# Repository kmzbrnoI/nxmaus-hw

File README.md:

# XNmaus

jednoduchý ovladač pro XpressNet

Důraz je kladen na nízkou výrobní cenu a dostupnost součástek.
Ovladač nemá display, adresa loko se mění jen vyjímečně.
Má jít o obdobu ovladače Fredi.

## Firmware

Program pro procesor je na adrese https://github.com/kmzbrnoI/nxmaus-fw

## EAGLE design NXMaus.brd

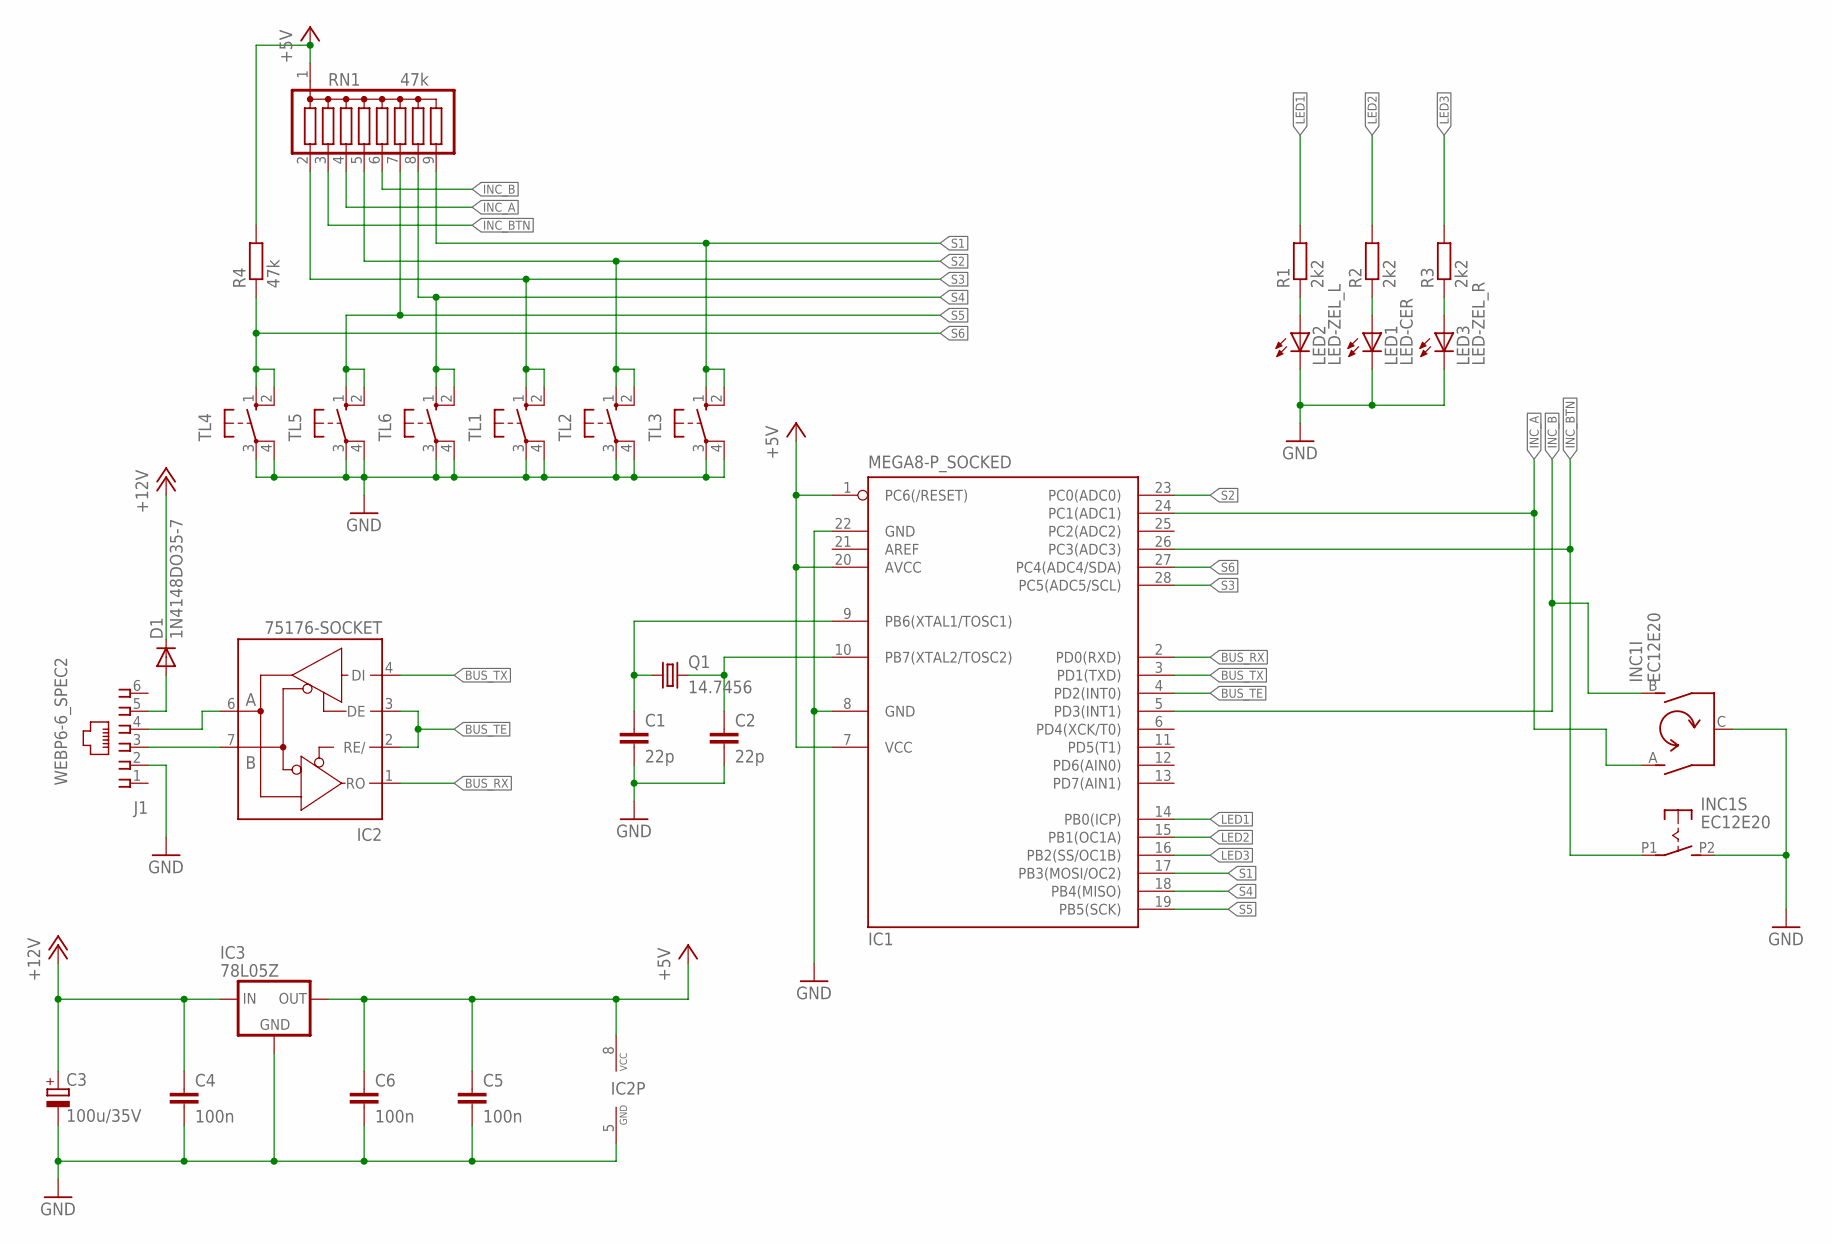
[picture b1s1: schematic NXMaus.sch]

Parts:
C1, C2: 22p; C025_050-025X075
C3: 100u/35V; E2,5-6
C4, C5, C6: 100n; C025_050-025X075
D1: 1N4148DO35-7; DO35-7
IC1: MEGA8-P_SOCKED; SOKL-28U
IC2: 75176-SOCKET; SOCKET-08
IC3: 78L05Z; TO92
INC1: EC12E20
J1: WEBP6-6_SPEC2
LED1: LED-CER; LED3MM
LED2: LED-ZEL_L; LED3MM
LED3: LED-ZEL_R; LED3MM
Q1: 14.7456; HC49U70
R1, R2, R3: 2k2; 0207/10
R4: 47k; R1206
RN1: 47k; SIL9
TL1, TL2, TL3, TL4, TL5, TL6: 10-XX; B3F-10XX

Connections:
+5V: C5.1, C6.1, IC1.1 (PC6(/RESET)), IC1.7 (VCC), IC1.20 (AVCC), IC2.8 (VCC), IC3.1 (VO), R4.2, RN1.1
+12V: C3.+, C4.1, D1.C, IC3.3 (VI)
BUS_A: IC2.6 (A), J1.4
BUS_B: IC2.7 (B), J1.3
BUS_RX: IC1.2 (PD0(RXD)), IC2.1 (RO)
BUS_TE: IC1.4 (PD2(INT0)), IC2.2 (RE/), IC2.3 (DE)
BUS_TX: IC1.3 (PD1(TXD)), IC2.4 (DI)
GND: C1.2, C1.3 (2), C2.2, C2.3 (2), C3.-, C4.2, C4.3 (2), C5.2, C5.3 (2), C6.2, C6.3 (2), IC1.8 (GND), IC1.22 (GND), IC2.5 (GND), IC3.2 (GND), INC1.C, INC1.P2 (S), J1.2, LED1.K (C), LED2.K (C), LED3.K (C), TL1.3, TL1.4 (P1), TL2.3, TL2.4 (P1), TL3.3, TL3.4 (P1), TL4.3, TL4.4 (P1), TL5.3, TL5.4 (P1), TL6.3, TL6.4 (P1)
INC_A: IC1.24 (PC1(ADC1)), INC1.A, RN1.4
INC_B: IC1.5 (PD3(INT1)), INC1.B, RN1.6
INC_BTN: IC1.26 (PC3(ADC3)), INC1.P1, RN1.3
LED1: IC1.14 (PB0(ICP)), R1.2
LED2: IC1.15 (PB1(OC1A)), R2.2
LED3: IC1.16 (PB2(SS/OC1B)), R3.2
unnamed: D1.A, J1.5
unnamed: LED3.A, R3.1
unnamed: LED1.A, R2.1
unnamed: C1.1, IC1.9 (PB6(XTAL1/TOSC1)), Q1.1
unnamed: C2.1, IC1.10 (PB7(XTAL2/TOSC2)), Q1.2
unnamed: LED2.A, R1.1
S1: IC1.17 (PB3(MOSI/OC2)), RN1.9, TL3.1 (S), TL3.2 (S1)
S2: IC1.23 (PC0(ADC0)), RN1.5, TL2.1 (S), TL2.2 (S1)
S3: IC1.28 (PC5(ADC5/SCL)), RN1.2, TL1.1 (S), TL1.2 (S1)
S4: IC1.18 (PB4(MISO)), RN1.8, TL6.1 (S), TL6.2 (S1)
S5: IC1.19 (PB5(SCK)), RN1.7, TL5.1 (S), TL5.2 (S1)
S6: IC1.27 (PC4(ADC4/SDA)), R4.1, TL4.1 (S), TL4.2 (S1)

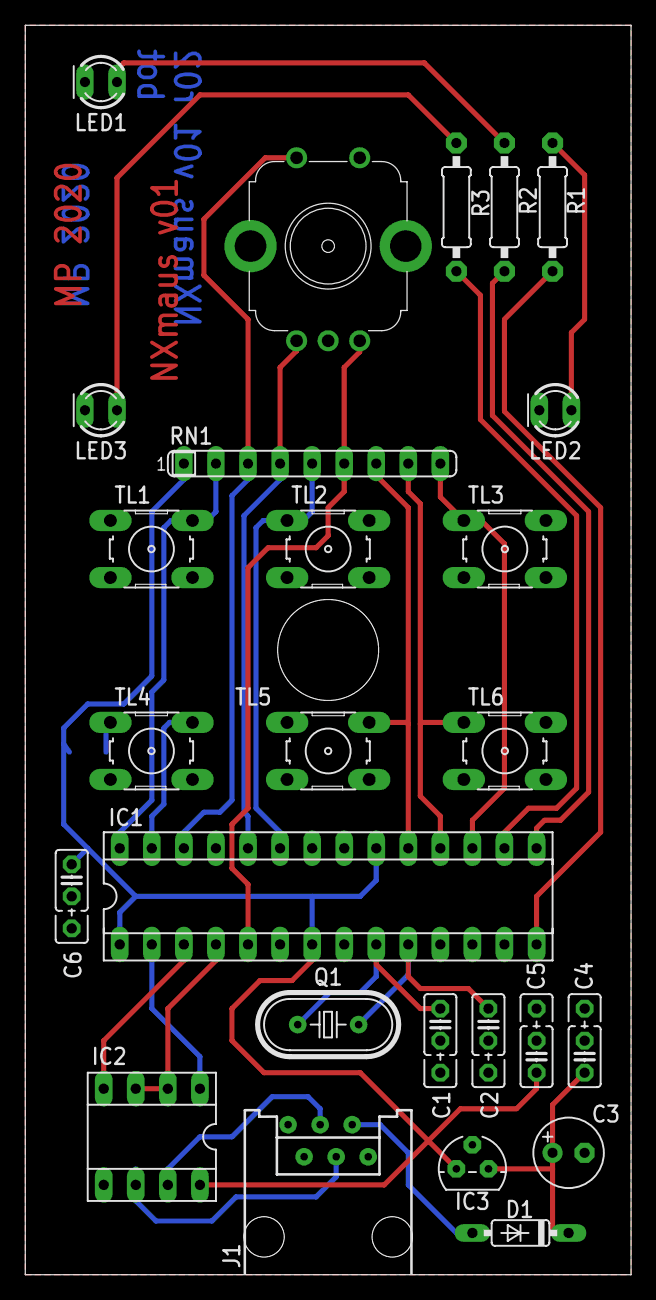
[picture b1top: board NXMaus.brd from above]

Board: 3 copper layers, 48.0 x 99.0 mm, 27 parts (1 on the bottom side), 26 nets.

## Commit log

2020-03-25 přidán README.md
